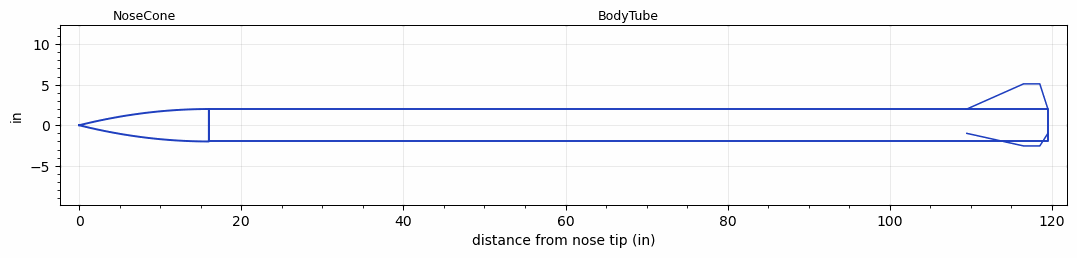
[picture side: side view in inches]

<RASAeroDocument>
 <FileVersion>2</FileVersion>
 <RocketDesign>
  <NoseCone>
   <Length>16</Length>
   <Diameter>4</Diameter>
   <Shape>Parabolic</Shape>
   <BluntRadius>0.1</BluntRadius>
   <Location>0</Location>
  </NoseCone>
  <BodyTube>
   <Length>103.5</Length>
   <Diameter>4</Diameter>
   <LaunchLugDiameter>0.7</LaunchLugDiameter>
   <LaunchLugLength>0.7</LaunchLugLength>
   <Location>16</Location>
   <Fin>
    <Count>3</Count>
    <Chord>10</Chord>
    <Span>3.105</Span>
    <SweepDistance>7</SweepDistance>
    <TipChord>2</TipChord>
    <Thickness>0.25</Thickness>
    <LERadius>0.125</LERadius>
    <Location>10</Location>
    <AirfoilSection>Double Wedge</AirfoilSection>
    <FX1>1</FX1>
   </Fin>
  </BodyTube>
  <Surface>Rough Camouflage Paint</Surface>
  <ModifiedBarrowman>True</ModifiedBarrowman>
  <Turbulence>False</Turbulence>
  <UseBooster1>False</UseBooster1>
  <UseBooster2>False</UseBooster2>
 </RocketDesign>
 <LaunchSite>
  <Altitude>180</Altitude>
  <Pressure>0</Pressure>
  <RodAngle>0</RodAngle>
  <RodLength>8</RodLength>
  <Temperature>90</Temperature>
  <WindSpeed>15</WindSpeed>
 </LaunchSite>
 <Recovery>
  <Altitude1>1000</Altitude1>
  <Altitude2>1500</Altitude2>
  <DeviceType1>Parachute</DeviceType1>
  <DeviceType2>Parachute</DeviceType2>
  <Event1>True</Event1>
  <Event2>True</Event2>
  <Size1>30.57</Size1>
  <Size2>96</Size2>
  <EventType1>Apogee</EventType1>
  <EventType2>Altitude</EventType2>
  <CD1>0.75</CD1>
  <CD2>2.2</CD2>
 </Recovery>
 <SimulationList>
  <Simulation>
   <SustainerEngine>M2500T  (AT)</SustainerEngine>
   <SustainerLaunchWt>58.4</SustainerLaunchWt>
   <SustainerNozzleDiameter>2</SustainerNozzleDiameter>
   <SustainerCG>68.7</SustainerCG>
   <SustainerIgnitionDelay>0</SustainerIgnitionDelay>
   <Booster1SeparationDelay>0</Booster1SeparationDelay>
   <Booster1IgnitionDelay>0</Booster1IgnitionDelay>
   <IncludeBooster1>False</IncludeBooster1>
   <Booster2Delay>0</Booster2Delay>
   <IncludeBooster2>False</IncludeBooster2>
   <TimetoApogee>30.86061</TimetoApogee>
   <MaxAltitude>15375.18</MaxAltitude>
   <MaxVelocity>1135.392</MaxVelocity>
  </Simulation>
  <Simulation>
   <SustainerEngine>M3400-WT  (CTI)</SustainerEngine>
   <SustainerLaunchWt>51.3</SustainerLaunchWt>
   <SustainerNozzleDiameter>2</SustainerNozzleDiameter>
   <SustainerCG>68</SustainerCG>
   <SustainerIgnitionDelay>0</SustainerIgnitionDelay>
   <Booster1SeparationDelay>0</Booster1SeparationDelay>
   <Booster1IgnitionDelay>0</Booster1IgnitionDelay>
   <IncludeBooster1>False</IncludeBooster1>
   <Booster2Delay>0</Booster2Delay>
   <IncludeBooster2>False</IncludeBooster2>
   <TimetoApogee>43.92863</TimetoApogee>
   <MaxAltitude>33809.3</MaxAltitude>
   <MaxVelocity>1898.891</MaxVelocity>
  </Simulation>
  <Simulation>
   <SustainerEngine>M2500T  (AT)</SustainerEngine>
   <SustainerLaunchWt>49.4</SustainerLaunchWt>
   <SustainerNozzleDiameter>2.5</SustainerNozzleDiameter>
   <SustainerCG>67</SustainerCG>
   <SustainerIgnitionDelay>0</SustainerIgnitionDelay>
   <Booster1SeparationDelay>0</Booster1SeparationDelay>
   <Booster1IgnitionDelay>0</Booster1IgnitionDelay>
   <IncludeBooster1>False</IncludeBooster1>
   <Booster2Delay>0</Booster2Delay>
   <IncludeBooster2>False</IncludeBooster2>
   <TimetoApogee>32.36058</TimetoApogee>
   <MaxAltitude>17986.97</MaxAltitude>
   <MaxVelocity>1342.551</MaxVelocity>
  </Simulation>
  <Simulation>
   <SustainerEngine>N2900-CL  (CTI)</SustainerEngine>
   <SustainerLaunchWt>65</SustainerLaunchWt>
   <SustainerNozzleDiameter>2</SustainerNozzleDiameter>
   <SustainerCG>73</SustainerCG>
   <SustainerIgnitionDelay>0</SustainerIgnitionDelay>
   <Booster1SeparationDelay>0</Booster1SeparationDelay>
   <Booster1IgnitionDelay>0</Booster1IgnitionDelay>
   <IncludeBooster1>False</IncludeBooster1>
   <Booster2Delay>0</Booster2Delay>
   <IncludeBooster2>False</IncludeBooster2>
   <TimetoApogee>43.92863</TimetoApogee>
   <MaxAltitude>33809.3</MaxAltitude>
   <MaxVelocity>1898.891</MaxVelocity>
  </Simulation>
 </SimulationList>
</RASAeroDocument>
